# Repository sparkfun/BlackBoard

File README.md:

SparkFun BlackBoard
============================

[  
*SparkFun BlackBoard (SPX-14669)*](https://www.sparkfun.com/products/14669)

The BlackBoard from SparkFun is everything you need in an Arduino Uno with *many* extra perks. BlackBoard has all of the hardware peripherals you know and love: 14 Digital I/O pins with 6 PWM pins, 6 Analog Inputs, UART, SPI and external interrupts. BlackBoard even has an SMD ISP header to connect SPI pins to shields.

We've applied every lesson we've learned about making a better Uno and created the BlackBoard. The USB to serial is now done with the ubiquitous CH340G requiring fewer driver installs and a rock solid microB connector with through hole anchoring. The power portion of the BlackBoard has been reworked: we upgraded the 3.3V regulator to provide up to 600mA, with full thermal and reverse circuit protection, and added extra decoupling capacitance to increase the sensitivity of the ADC readings. We've decreased the brightness of the power, 13, and TX/RX LEDs from blinding to just perfect. We've added 3.3V voltage translation and a [Qwiic connector](https://www.sparkfun.com/qwiic) to the edge of the board to allow for quick and seamless connection to our ever-growing line of I<sup>2</sup>C based [Qwiic](https://www.sparkfun.com/qwiic) products. 

And for more advanced users we've added a 3.3V/5V I/O jumper. Cut the trace to 5V and solder a jumper to the 3.3V side and the board will run at 3.3V. This is extremely handy if you have a shield or 3.3V sensitive devices, such as an SPI interface, that needs protecting.

The SparkFun BlackBoard comes fully tested with the Optiboot bootloader and can be easily programmed with the 'Arduino/Genuino Uno' option from within Arduino. You can power the BlackBoard over USB or through the barrel jack. The on-board power regulator can handle anything from 7 to 15VDC. Check out the related items below for a compatible wall-wart power supply.

Not sure which Arduino or Arduino-compatible board is right for you? Check out our [Arduino Buying Guide](https://www.sparkfun.com/arduino_guide)!

Repository Contents
-------------------
* **/Documentation** - Data sheets, additional product information
* **/Hardware** - Eagle design files (.brd, .sch)

License Information
-------------------

This product is _**open source**_! 

Please review the LICENSE.md file for license information. 

If you have any questions or concerns on licensing, please contact techsupport@sparkfun.com.

Please use, reuse, and modify these files as you see fit. Please maintain attribution to SparkFun Electronics and release any derivative under the same license.

Distributed as-is; no warranty is given.

- Your friends at SparkFun.

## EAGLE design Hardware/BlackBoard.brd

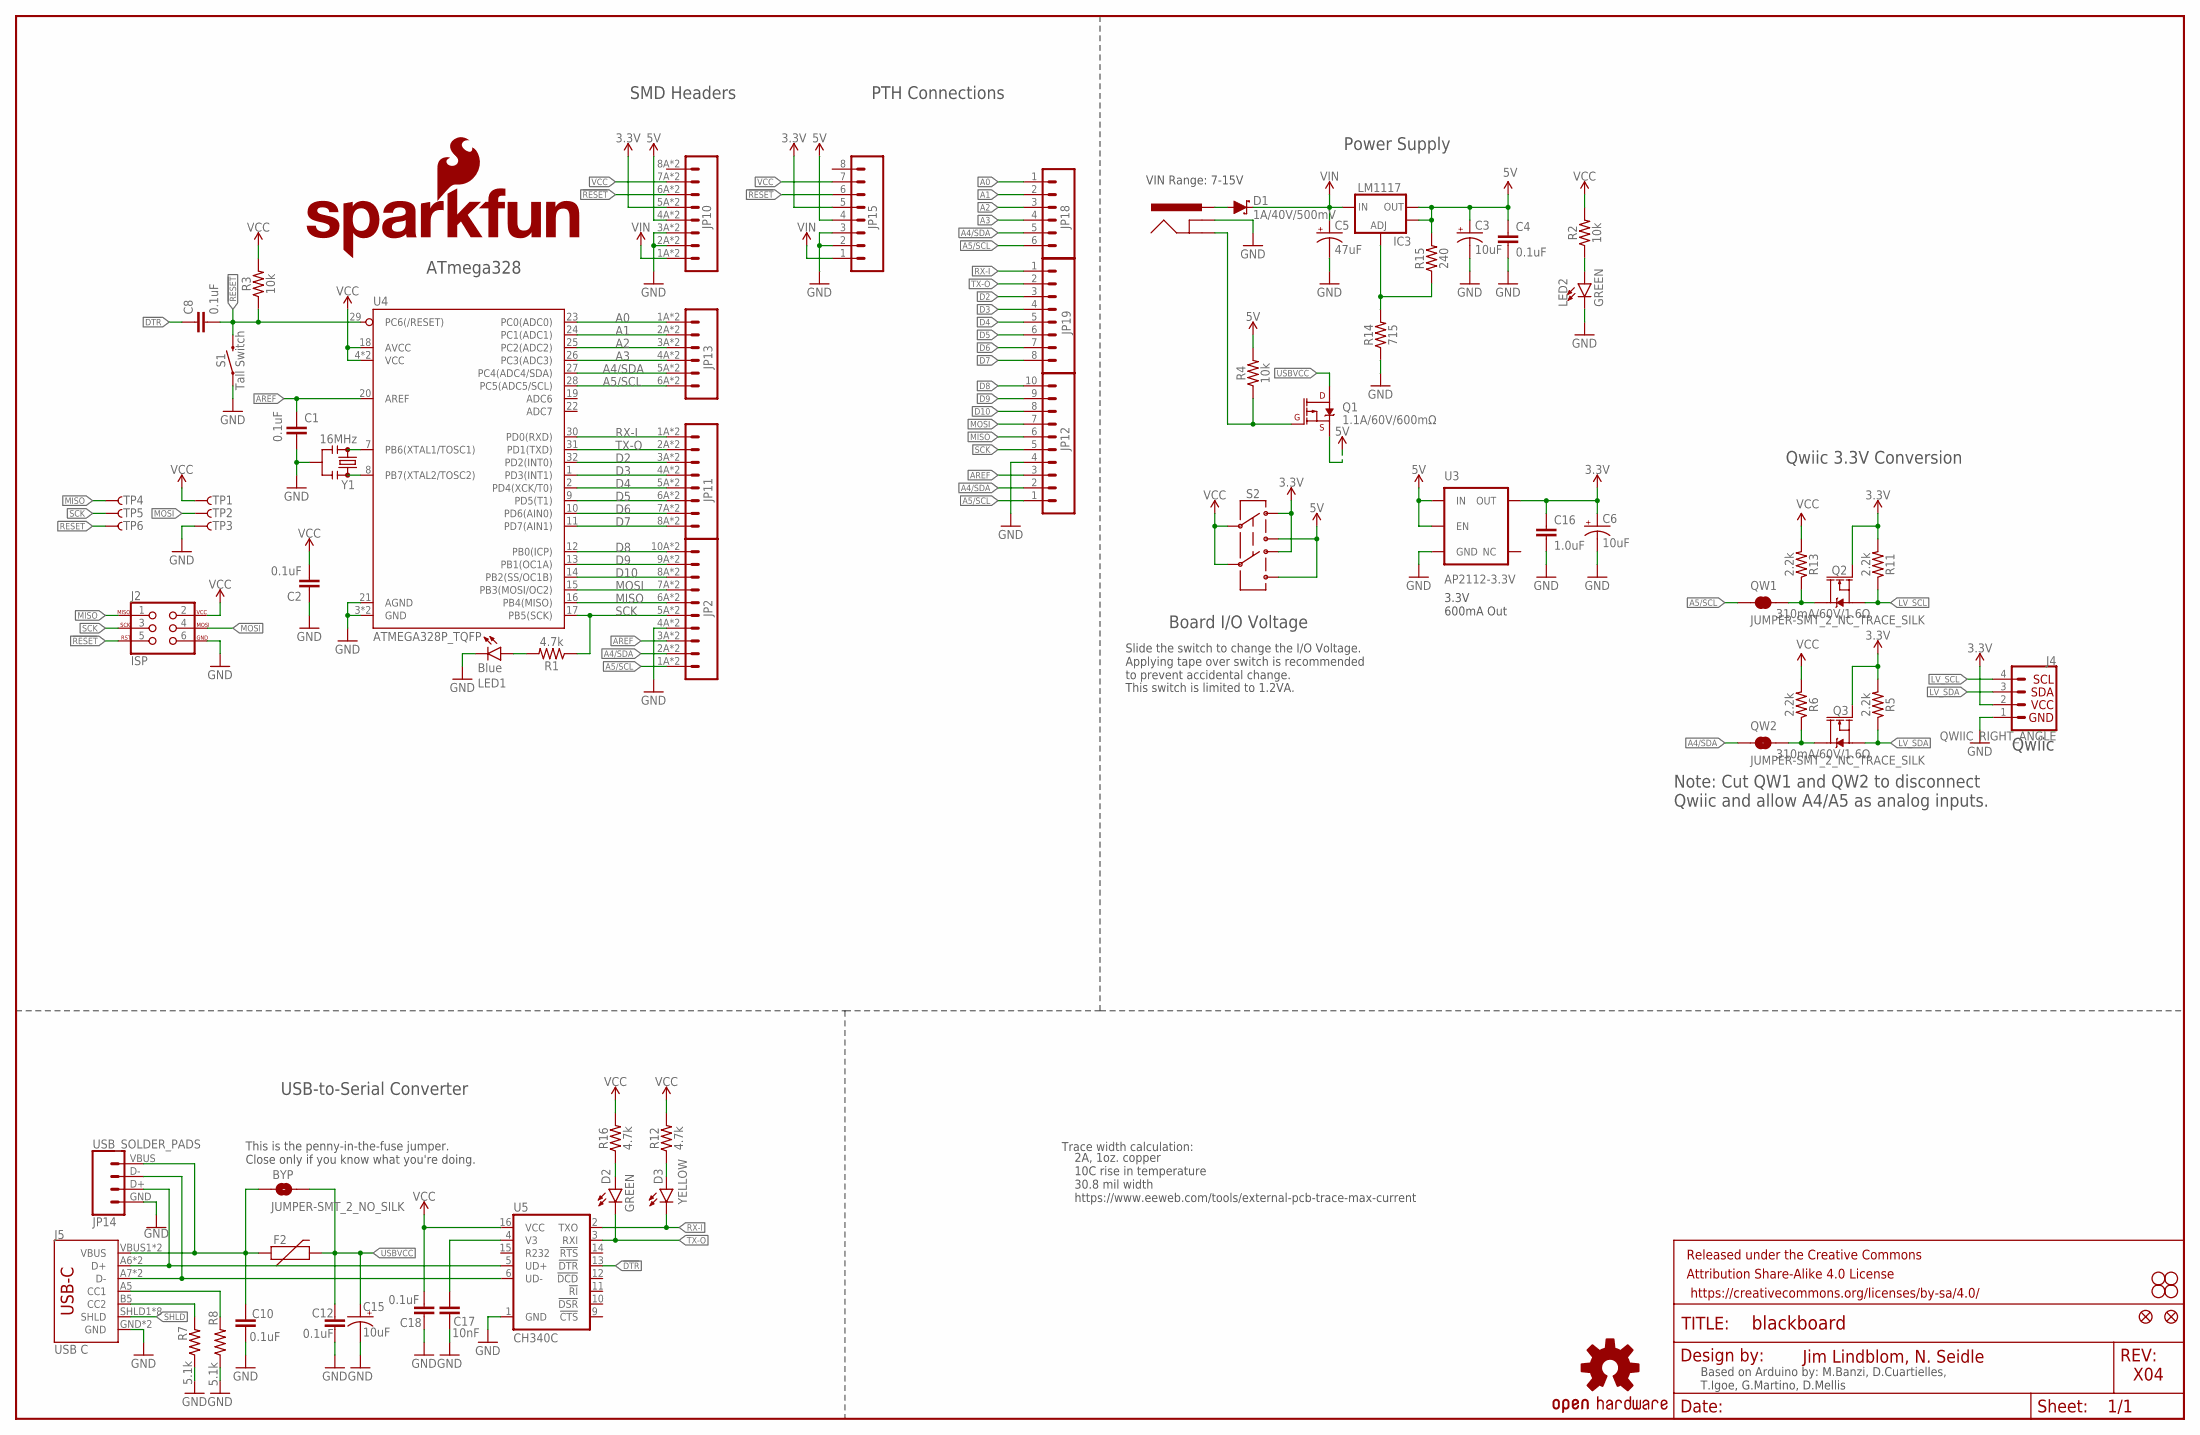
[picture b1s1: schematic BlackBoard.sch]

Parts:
BYP: JUMPER-SMT_2_NO_SILK; SMT-JUMPER_2_NO_SILK
C1, C2, C4, C8, C10, C12, C18: 0.1uF; 0603
C3, C6, C15: 10uF; EIA3216
C5: 47uF; PANASONIC_D
C16: 1.0uF; 0603
C17: 10nF; 0603
D1: 1A/40V/500mV; SMA-DIODE
D2: GREEN; LED-1206
D3: YELLOW; LED-1206-HIDDENSILK
F2: 6V/2A; 1210
FRAME1: FRAME-LEDGER; CREATIVE_COMMONS
IC3: LM1117; SOT223-ALT1
J2: ISP; 2X3_SMT_POSTS
J3: POWER_JACKSUPER_BOMB_DIGITY; POWER_JACK_SMD_OVERPASTE_SUPER_BOMB_DIGITY
J4: QWIIC_RIGHT_ANGLE; JST04_1MM_RA
J5: USB C; USB-C-16P
JP1: SFE_LOGO_NAME.1_INCH; SFE_LOGO_NAME_.1
JP2: M10SMD_COMBO; 1X10_SMD_COMBINED
JP3, JP4, JP5, JP6: STAND-OFF
JP7: SFE_LOGO_FLAME.1_INCH; SFE_LOGO_FLAME_.1
JP8, JP9: FIDUCIAL1X2; FIDUCIAL-1X2
JP10: M08SMD-COMBO; 1X08_SMD_COMBINED@1
JP11: JP11; 1X08_SMD_COMBINED@1
JP12: M10NO_SILK; 1X10_NO_SILK
JP13: M06SMD-STRAIGHT-COMBO; 1X06_SMD_STRAIGHT_COMBO
JP14: USB_SOLDER_PADS; USB-SOLDER-PADS
JP15: M08NO_SILK; 1X08_NO_SILK@1
JP18: M06NO_SILK; 1X06_NO_SILK@1
JP19: CONN_08NO_SILK_FEMALE_PTH; 1X08_NO_SILK
LED1: Blue; LED-1206-HIDDENSILK
LED2: GREEN; LED-1206
Q1: 1.1A/60V/600mΩ; SOT23-3
Q2, Q3: 310mA/60V/1.6Ω; SOT323
QW1, QW2: JUMPER-SMT_2_NC_TRACE_SILK; SMT-JUMPER_2_NC_TRACE_SILK
R1, R12, R16: 4.7k; 0603
R2, R3, R4: 10k; 0603
R5, R6, R11, R13: 2.2k; 0603
R7, R8: 5.1k; 0603
R14: 715; 0603
R15: 240; 0603
S1: Tall Switch; TACTILE_SWITCH_SMD_5.2MM
S2: SWITCH-DPDT-SMD-AYZ0202; SWITCH_DPDT_SMD_AYZ0202
TP1, TP2, TP3, TP4, TP5, TP6: TP-3x5; PAD.03X.05
U3: AP2112-3.3V; SOT23-5
U4: ATMEGA328P_TQFP; TQFP32-08
U5: CH340C; SO016
U$16: OSHW-LOGOS; OSHW-LOGO-S
Y1: 16MHz; RESONATOR-SMD-3.2X1.3

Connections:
3.3V: C6.+, C16.1, J4.2, JP10.5A (5), JP10.5B (5), JP15.5, Q2.1 (G), Q3.1 (G), R5.2, R11.2, S2.1, S2.4, U3.5 (OUT)
5V: C3.+, C4.1, IC3.2 (OUT), IC3.4 (OUT), JP10.4A (4), JP10.4B (4), JP15.4, Q1.2 (S), R4.2, R15.2, S2.3, S2.6, U3.1 (IN), U3.3 (EN)
!DTR: C8.1, U5.13 (!DTR)
!RESET: C8.2, J2.5, JP10.6A (6), JP10.6B (6), JP15.6, R3.1, S1.3 (2), S1.4 (2), TP6.P$1, U4.29 (PC6(/RESET))
A0: JP13.1A (1), JP13.1B (1), JP18.1, U4.23 (PC0(ADC0))
A1: JP13.2A (2), JP13.2B (2), JP18.2, U4.24 (PC1(ADC1))
A2: JP13.3A (3), JP13.3B (3), JP18.3, U4.25 (PC2(ADC2))
A3: JP13.4A (4), JP13.4B (4), JP18.4, U4.26 (PC3(ADC3))
A4/SDA: JP2.2A (2), JP2.2B (2), JP12.2, JP13.5A (5), JP13.5B (5), JP18.5, QW2.1, U4.27 (PC4(ADC4/SDA))
A5/SCL: JP2.1A (1), JP2.1B (1), JP12.1, JP13.6A (6), JP13.6B (6), JP18.6, QW1.1, U4.28 (PC5(ADC5/SCL))
AREF: C1.1, JP2.3A (3), JP2.3B (3), JP12.3, U4.20 (AREF)
CC1: J5.A5 (CC1), R8.2
CC2: J5.B5 (CC2), R7.2
D2: JP11.3A (3), JP11.3B (3), JP19.3, U4.32 (PD2(INT0))
D3: JP11.4A (4), JP11.4B (4), JP19.4, U4.1 (PD3(INT1))
D4: JP11.5A (5), JP11.5B (5), JP19.5, U4.2 (PD4(XCK/T0))
D5: JP11.6A (6), JP11.6B (6), JP19.6, U4.9 (PD5(T1))
D6: JP11.7A (7), JP11.7B (7), JP19.7, U4.10 (PD6(AIN0))
D7: JP11.8A (8), JP11.8B (8), JP19.8, U4.11 (PD7(AIN1))
D8: JP2.10A (10), JP2.10B (10), JP12.10, U4.12 (PB0(ICP))
D9: JP2.9A (9), JP2.9B (9), JP12.9, U4.13 (PB1(OC1A))
D10: JP2.8A (8), JP2.8B (8), JP12.8, U4.14 (PB2(SS/OC1B))
D+: J5.A6 (D+), J5.B6 (D+), JP14.D+ (3), U5.5 (UD+)
D-: J5.A7 (D-), J5.B7 (D-), JP14.D- (2), U5.6 (UD-)
GND: C1.2, C2.1, C3.-, C4.2, C5.-, C6.-, C10.2, C12.2, C15.-, C16.2, C17.2, C18.2, J2.6, J3.GND (GNDBREAK), J4.1, J5.GND, J5.GND2 (GND), JP2.4A (4), JP2.4B (4), JP10.2A (2), JP10.2B (2), JP10.3A (3), JP10.3B (3), JP12.4, JP14.GND (4), JP15.2, JP15.3, LED1.C, LED2.C, R7.1, R8.1, R14.1, S1.1, S1.2 (1), TP3.P$1, U3.2 (GND), U4.3 (GND), U4.5 (GND), U4.21 (AGND), U5.1 (GND), Y1.2
INSERT: J3.P$4 (GND), Q1.1 (G), R4.1
LV_SCL: J4.4, Q2.2 (S), R11.1
LV_SDA: J4.3, Q3.2 (S), R5.1
MISO: J2.1, JP2.6A (6), JP2.6B (6), JP12.6, TP4.P$1, U4.16 (PB4(MISO))
MOSI: J2.4, JP2.7A (7), JP2.7B (7), JP12.7, TP2.P$1, U4.15 (PB3(MOSI/OC2))
unnamed: LED1.A, R1.2
unnamed: LED2.A, R2.1
unnamed: U4.7 (PB6(XTAL1/TOSC1)), Y1.1
unnamed: U4.8 (PB7(XTAL2/TOSC2)), Y1.3
unnamed: D2.A, R16.1
unnamed: C17.1, U5.4 (V3)
unnamed: Q2.3 (D), QW1.2, R13.1
unnamed: D3.A, R12.1
unnamed: IC3.1 (ADJ), R14.2, R15.1
unnamed: Q3.3 (D), QW2.2, R6.1
PWRIN: D1.A, J3.VIN0 (PWR)
RX-I: D3.C, JP11.1A (1), JP11.1B (1), JP19.1, U4.30 (PD0(RXD)), U5.2 (TXO)
SCK: J2.3, JP2.5A (5), JP2.5B (5), JP12.5, R1.1, TP5.P$1, U4.17 (PB5(SCK))
SHLD: J5.SHLD1 (SHLD), J5.SHLD2 (SHLD), J5.SHLD3 (SHLD), J5.SHLD4 (SHLD), J5.SHLD5 (SHLD), J5.SHLD6 (SHLD), J5.SHLD7 (SHLD), J5.SHLD8 (SHLD)
TX-O: D2.C, JP11.2A (2), JP11.2B (2), JP19.2, U4.31 (PD1(TXD)), U5.3 (RXI)
USBVCC: BYP.2, C12.1, C15.+, F2.2, Q1.3 (D)
VCC: C2.2, C18.1, J2.2, JP10.7A (7), JP10.7B (7), JP15.7, R2.2, R3.2, R6.2, R12.2, R13.2, R16.2, S2.2, S2.5, TP1.P$1, U4.4 (VCC), U4.6 (VCC), U4.18 (AVCC), U5.16 (VCC)
VIN: C5.+, D1.C, IC3.3 (IN), JP10.1A (1), JP10.1B (1), JP15.1
VUSB: BYP.1, C10.1, F2.1, J5.VBUS1 (VBUS), J5.VBUS2 (VBUS), JP14.VBUS (1)

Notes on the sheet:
Power Supply
ATmega328
USB-to-Serial Converter
Based on Arduino by: M.Banzi, D.Cuartielles, T.Igoe, G.Martino, D.Mellis
Jim Lindblom, N. Seidle
X04
VIN Range: 7-15V
3.3V 600mA Out
Board I/O Voltage
Slide the switch to change the I/O Voltage. Applying tape over switch is recommended to prevent accidental change.
Qwiic
Qwiic 3.3V Conversion
Note: Cut QW1 and QW2 to disconnect Qwiic and allow A4/A5 as analog inputs.
This is the penny-in-the-fuse jumper. Close only if you know what you're doing.
Trace width calculation:
2A, 1oz. copper 10C rise in temperature 30.8 mil width https://www.eeweb.com/tools/external-pcb-trace-max-current
This switch is limited to 1.2VA.
PTH Connections
SMD Headers

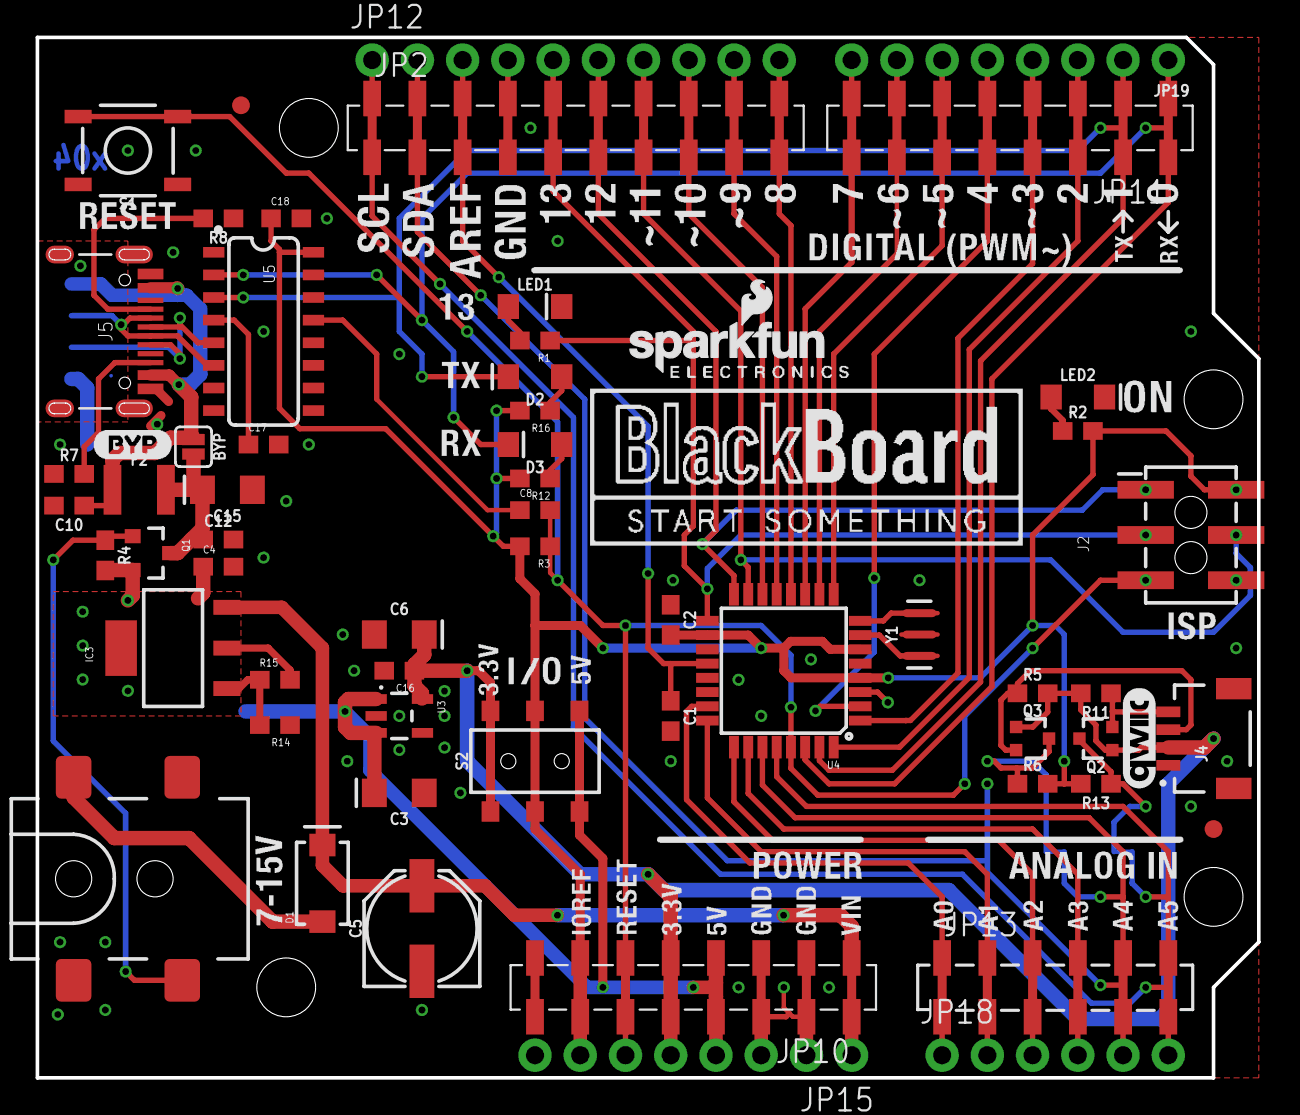
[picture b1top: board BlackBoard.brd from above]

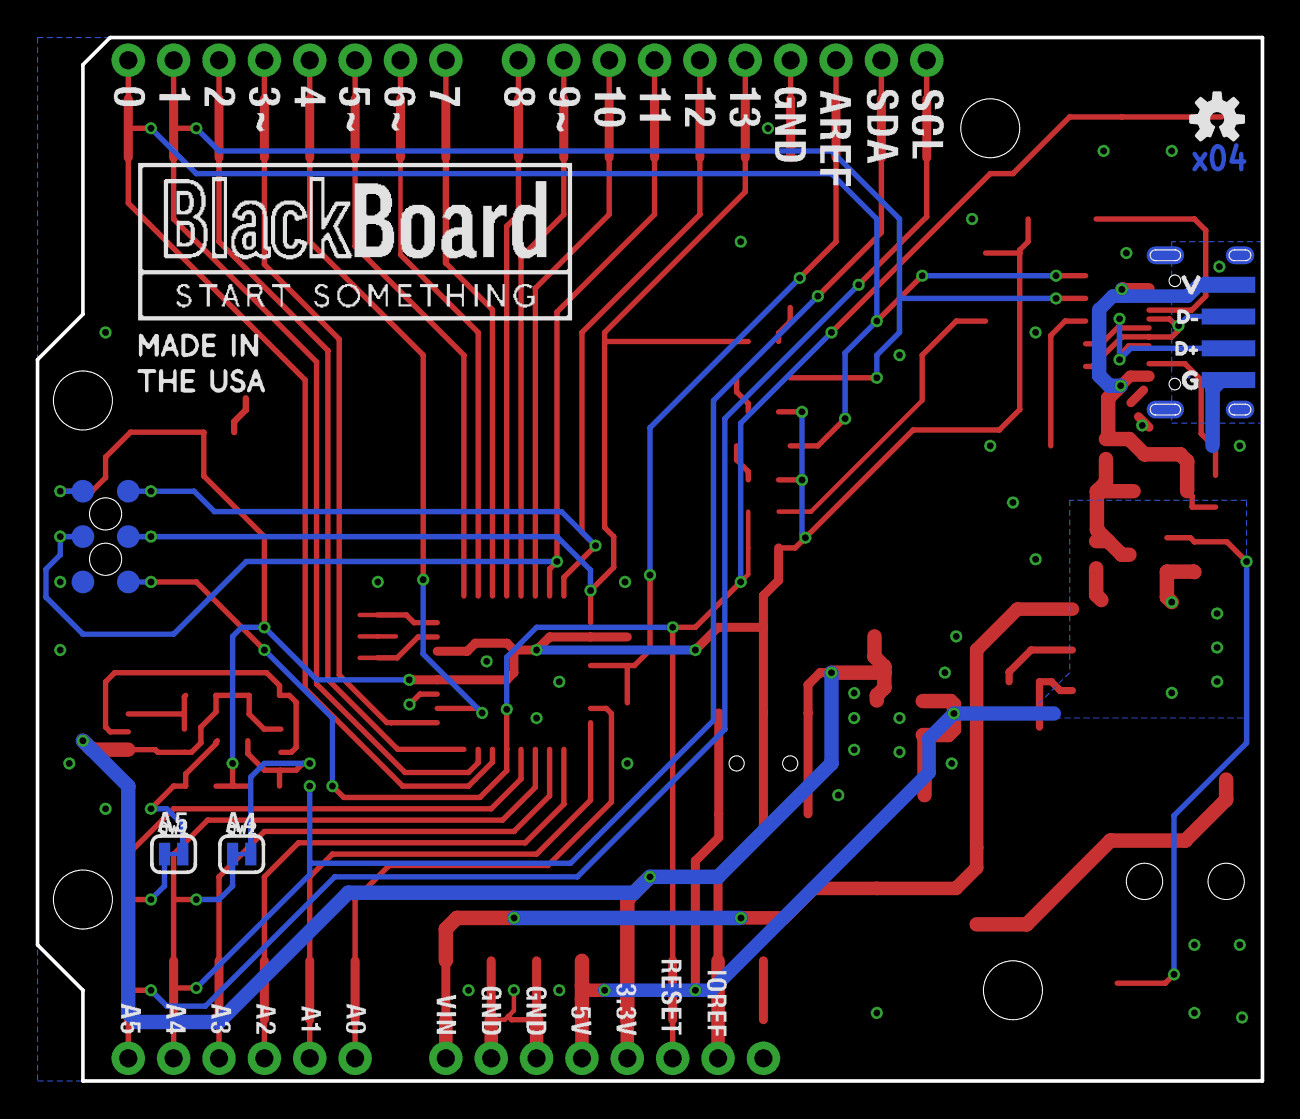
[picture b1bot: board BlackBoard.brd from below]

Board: 2 copper layers, 68.6 x 58.4 mm, 84 parts (16 on the bottom side), 49 nets.

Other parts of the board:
U$1, U$3: BLACKBOARDLOGO#PNG
U$2: D#3
U$4: MADEINUSA#PNG
U$9: QWIIC_COPYRIGHT_SMALL
U$10: D#4
U$11: G1
U$12: V0
U$68: BYP0

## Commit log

2018-04-30 Small schematic changes
2018-04-30 Readme update. Schematic compression.
2018-11-19 Add USB pads for external connector
2018-11-19 Removing old gerbers. Adding production panel.
2019-01-10 Cleanup for release of v2
2019-02-21 Swap to larger PTC. Correct connection to IOREF.
2019-03-13 Adding panel
2020-01-27 Add switch for IO voltage. Add PTH holes.
2020-01-27 Adjust silk on PTH headers
2020-01-27 Add panel files

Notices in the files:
parts and their libraries:
SparkFun-Aesthetics: Licensing: CC v3.0 Share-Alike You are welcome to use this library for commercial purposes.
SparkFun-Aesthetics: Released under the Creative Commons Attribution Share-Alike 4.0 License
SparkFun-Aesthetics: https://creativecommons.org/licenses/by-sa/4.0
